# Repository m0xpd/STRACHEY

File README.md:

# STRACHEY

STRACHEY is a new kind of sequencer for electronic music applications. 

STRACHEY's novelty is two-fold: 
* it directly implements my [tuning strategy](https://github.com/m0xpd/TuningStrategyForVoltages) for Klee-type sequencers and
* it introduces a dynamic [Permutation Matrix](https://en.wikipedia.org/wiki/Permutation_matrix) between the gates and the weights, adding a new dimension of variability

I you wish to build one, or if you're just curious, you can read or download [details of the hardware, including PCB and front panel designs](https://github.com/m0xpd/STRACHEY/tree/main/Hardware) and [a listing of the controller code](https://github.com/m0xpd/STRACHEY/tree/main/Controller).

There are some [specifications here](https://github.com/m0xpd/STRACHEY/blob/main/README.md#specifications) and some details of [Calibration and Configuration here](https://github.com/m0xpd/STRACHEY/blob/main/README.md#calibration-and-configuration). 

I have produced an [Introductory video](https://youtu.be/6UQzKo1PWnU), which describes and demonstrates STRACHEY in detail. 

Further description of STRACHEY follows below.

STRACHEY is published under a Creative Commons BY-SA 4.0 [License](https://github.com/m0xpd/STRACHEY/blob/main/LICENSE.txt). 

# Background

The STRACHEY sequencer is named for [Christopher Strachey](https://en.wikipedia.org/wiki/Christopher_Strachey), who (amongst many other accomplishments) was the first person in England to [program a computer to make music](https://link.springer.com/chapter/10.1007/978-3-319-53280-6_8), leading to the world's [first recording of computer-generated music](http://curation.cs.manchester.ac.uk/digital60/www.digital60.org/media/mark_one_digital_music/mark_one_digital_music.mp3).

Christopher Strachey developed [one of the world's first computer games](https://historyofinformation.com/detail.php?entryid=3731), and developed the programming language CPL, a precursor of C (which is used in the code which runs this STRACHEY sequencer).

STRACHEY implements my [Tuning Strategy for Klee-type Sequencers](https://github.com/m0xpd/TuningStrategyForVoltages) and, as such, 
it is directly inspired by Music Thing Modular's [Turing Machine](https://www.musicthing.co.uk/Turing-Machine/) and its [Voltages expander](https://www.musicthing.co.uk/Turing-Volts-Expander/). STRACHEY was built on my own experiences and habits, formed when using the Turing Machine with its Voltages expander; STRACHEY tries to capture and make accessible all which I found *musically useful* within the vast space covered by the Turing Machine. 

STRACHEY contains an implementation of the Turing Machine ('TM'). The control labelled "TURING" at top left of the module (and the associated CV input) is the equivalent of the large, conspicuous knob on the original TM hardware, and operates in exactly the same way. 

STRACHEY offers (almost) all the features of the original hardware, including the ability to interface to expanders, such as [Pulses](https://www.musicthing.co.uk/Turing-Pulse-Expander/), [Volts](https://www.musicthing.co.uk/Turing-Volts-Expander/) and even [Voltages](https://www.musicthing.co.uk/Turing-Volts-Expander/). It even adds several new features to its TM implementation (such as the START output and CV control over both the Length parameter and the Write function).

More importantly, STRACHEY directly implements the fixed tunings presented in my [Tuning Strategy](https://github.com/m0xpd/TuningStrategyForVoltages), without the need to set these up on the sliders of a Voltages expander, which is a laborious and delicate task. This offers opportunity to quickly expand and develop the tunings (e.g. using octave expansions) and - uniquely - to instantly *move between* the tunings, allowing modulations and "chord progressions" to be explored. However, STRACHEY does more...

STRACHEY has three channels of analog output: A, B and Y, all of which derive their timing from a master clock. 

STRACHEY's clock signal can be applied from an external source to the Clock input (as in the TM). In the absence of an external signal, a clock is generated by a simple oscillator integral to STRACHEY. Outputs A and Y both appear on every beat of this clock.

Channel Y is the conventional TM 'OUT' signal, formed of a weighted sum of the TM's gates 1:8  (the weights being an exponential series, proportional to 1, 0.5, 0.25, 0.125, ...). STRACHEY's Y output is scaled to range between 0 and 5V and is provided for use as a general modulation source.

Channel A is the main STRACHEY output. It produces an output (to be interpreted as a 1V/octave pitch CV signal) at the rate of the main signal clock. 
It is set to span six and a half octaves at a resolution of 51 quantisation steps per semitone, meaning there will be less than a 2 cent error in tuning over the system's range, if we can trust the DAC linearity (experience to date has been entirely positive).

# STRACHEY Tunings

The control at top right of the panel, labelled "TUNING", and the associated CV input choose between 24 pre-detemined settings of "weights", equivalent to the slider settings on a Turing Machine 'VOLTAGES' expander, or the knobs on any other sequencer. These weights, together with the gates generated by the Turing Machine, form the channel A (and channel B) outputs.

The weight settings are called 'Tunings' and they are chosen from my [Tuning Strategy](https://github.com/m0xpd/TuningStrategyForVoltages) to be those which give an output which I found to be musically useful. 

The tunings are arranged in three Banks; 
* Bank A are "Basic" Tunings, mainly yielding arpeggiated chords 
* Bank B are mainly MODES
* Bank C are mainly [Symmetric Scales](https://en.wikipedia.org/wiki/Symmetric_scale)

The tunings presently implemented in the code are tabulated below:

| Tuning# | Description | Tuning Strategy # | Bank | Display |
|---|---|---|---|---|
| 0 | Root & Fifth | (3) | A | 10000000 |
| 1 | AEOLIAN (Natural minor) | 14 | A | 01000000 |
| 2 | Minor 7th | 5 | A | 00100000 |
| 3 | Major 7th | 6 | A | 00010000 |
| 4 | Diminished 7th | 8 | A | 00001000 |
| 5 | Augmented | 7 | A | 00000100 |
| 6 | "Sus 7th" Feel | 10 | A | 00000010 |
| 7 | "9th" Feel | 9 | A | 00000001 |
| 8 | Root & Fifth | (3) | A | 10000000 |
| 9 | AEOLIAN | 14 | B | 01000000 |
| 10 | DORIAN | 11 | B | 00100000 |
| 11 | PHRYGIAN | 13 | B | 00010000 |
| 12 | IONIAN | 18 | B | 00001000 |
| 13 | Hexatonic, IONIAN, missing 7th degree | 22 | B | 00000100 |
| 14 | Octatonic, IONIAN, with added flat 5 | 20 | B | 00000010 |
| 15 | Hexatonic, with no third | 23 | B | 00000001 |
| 16 | Root & Octave | (3) | C | 10000000 |
| 17 | Tritone | (15) | C | 01000000 |
| 18 | Augmented | 7 | C | 00100000 |
| 19 | Diminshed | 8 | C | 00010000 |
| 20 | Whole-tone | 16 | C | 00001000 |
| 21 | Chromatic | 17 | C | 00000100 |
| 22 | Major (IONIAN) | 19 | C | 00000010 |
| 23 | Descending Major Scale | N/A | C | 00000001 |

'Bank' (fourth column of the table above) is indicated by the stack of three LEDs in the centre, top of the module. Bank A is indicated by the lowest LED.

'Display' (final column of the table) shows the pattern illuminated on the 'TUNING' LEDs.

A bracket surrounding the Tuning Strategy number in the table above indicates that it is slightly modified relative to the tuning given in the Tuning Strategy document (e.g. by the addition of a second flattened fifth to the tritone, to allow it to sound the octave). Tuning # 23 is unusual and is not derived from the Tuning Strategy. It is included as a test/demonstration case. Tuning # 23  does generate 12TET outputs, but it doesn't produce a particularly pleasant output when used with a gate sequences having more than one active gate. It is intended to be used with a **single active gate**, when it will be heard as a descending major scale.

Some tunings are intentionally repeated in the table above for ease of use - some *appear* repeated, but are different forms (such as the several versions of IONIAN [major scale] tuning which are presented).

STRACHEY goes on to develop outputs using these initial tunings by a series of modifications and manipulations, which are now described.

# Weight Modifications in STRACHEY

Channel B is the secondary STRACHEY output. It operates at the same pitch resolution as channel B but (for reasons which are explained below), the pitch range of channel B is lower than that of channel A. 

The outputs on channel B occur at the onsets of a Euclidean pattern, generated by STRACHEY. This pattern has length determined by the Turing Machine's LENGTH parameter and density determined by STRACHEY's DENSITY controls. LENGTH and DENSITY are both controllable by front panel potentiometers - "DENSITY" is the third of STRACHEY's main potentiometers. Both Length and Density and can further be controlled by CV inputs. 

This makes the onsets of the output from channel B: 

* a subset of the beats of the main system clock,
* a pattern which has rhythmic interest and
* a pattern which can be made to change (by modulating the Density CV input)

The same gate sequence (generated by the Turing Machine) and the same initial weight vector (selected by the TUNING controls) produce the channel A and B outputs, so the *set of allowed pitches* are the same (as described at tedious length in the [Tuning Strategy](https://github.com/m0xpd/TuningStrategyForVoltages)). However, STRACHEY can apply two modifications to the weight vector used in forming the output from channel A. 

Firstly, the initial weight vector can be permuted (i.e. changed in order) before channel A's output is formed, during operation, giving STRACHEY an entirely new dimension of variability relative to other Klee sequencers, including the Turing Machine. STRACHEY performs these permutations using different "Methods", selected by the METHOD control (and associated CV input). These permutations are triggered by "Change" commands, issued either by the CHANGE pushbutton (or the associated CV input). A fuller description appears below. 

Secondly, the initial weight vector can be subject to additions, each of which cause an octave increase in pitch span (under control of the SPAN controls - both potentiometer and CV input). These extend the pitch range of the channel A output, using the same notes as specified in the original tuning, but allowing them to range over a wider span. 

Neither the permutations or the octave extensions of channel A's weight vector are applied to channel B.

So - channel B has a generally reduced pitch span compared to channel A (as there is no octave extension added via SPAN) and there is no variation introduced by permutation. It also has less dense onsets; it '*samples*' notes from the set of pitches within the fundamental range of channel A's pitch distribution on a rhythmic sub-pattern of variable DENSITY. Channel B is particularly useful for forming bass or melody against a fuller, arpeggiated 'continuo' from channel A.

# Permuting the Weights of a Step Sequencer

The idea of introducing permutation between the gates and weights of a Random Looping Sequencer is (as far as I'm aware) novel. 

The practice of stopping and single-stepping a sequencer is, of course, familiar and I have [demonstrated some other effects](https://www.youtube.com/watch?v=kFBzPTS7XLM) obtained with multi-rate or asynchronous scanning of a Klee sequencer. But synchronous permutation of the mapping between gates and weights is less familiar. One notable exception is the idea of reversing the scan direction of a sequencer, (which can be expressed as a simple permutation) and is seen on both 'DIY' sequencers from [MFOS](https://musicfromouterspace.com/analogsynth_new/SEQ16_2006/SEQ16_2006.php) and commercial units from e.g. [Doepfer](https://doepfer.de/a154.htm). 

STRACHEY can - of course - reverse its scan direction, either by flipping the current permutation (Method# 13)  or by resetting to a 'reversed' version of the starting weight vector (Method# 12).

There are other synchronous permutations worth exploring.

Back in 2017 I made a gate sequencer 

which was inspired by patterns used in [Change Ringing](https://en.wikipedia.org/wiki/Change_ringing), a perversely English way of sounding the bells of a Church. These patterns are called "Methods". The key ingredient of Change Ringing is an exploration of the permutations by which a number of bells may be sounded in sequence. In the case of my module, I implemented four of the traditional "Methods"  ([Rounds](https://jaharrison.me.uk/Ringing/Glossary/R.html#rounds), [Plain Hunt](https://en.wikipedia.org/wiki/Plain_hunt), [Grandsire](https://en.wikipedia.org/wiki/Grandsire) and [Plain Bob](https://www.ringing.info/plp/pb8/index.html)) to trigger any number of gates (any "[Stage](https://jaharrison.me.uk/Ringing/Glossary/S.html#stage)") between 4 and 8. Although the sequencer was made as a percussion trigger source rather than in attempt to simulate the sound of church bells, I added - for the purposes of demonstration - two 1V/octave pitch CV outputs, one set to be typical of the diatonic tuning of a ring of bells and one set (for comedic purposes!) to a minor pentatonic scale. 

I was, therefore, entirely familiar with the idea of using permutations in general (and permutations from bell ringing in particular) in a step sequencer. The only further inventive step for me in the development of STRACHEY was the extension of these ideas to a Klee-type sequencer. 

That step involved the introduction of a [permutation matrix](https://en.wikipedia.org/wiki/Permutation_matrix) between the gates and the weights in the scalar product which forms the sequencer output - for both a conventional sequencer and a Klee sequencer. (The actual coding doesn't require matrix methods - it is achieved in [the code](https://github.com/m0xpd/STRACHEY/blob/main/Controller/Code/STRACHEY_Sequencer_1v0.ino) just by indexing within the scalar product. The matrix is just a conceptual and mathematical convenience.)

STRACHEY uses a fixed number of weights ("Stage") to form the pitch output from the gate vector: the eight inherited from the 8 sliders on MTM's Voltages expander. If these 8 weights are seen in analogy with 8 bells (which is the standard stage in a larger bell tower for change ringing), some of STRACHEY's methods for permuting the weights can be related to bell ringing.

STRACHEY currently implements two standard bell ringing methods; "[rounds](https://jaharrison.me.uk/Ringing/Glossary/R.html#rounds)" (which is the bell-ringing term when the permuatation matrix is fixed at the identity matrix)  and "Plain Hunt Major" ('Plain Hunt' is - as we've seen - a [standard algorithm](https://en.wikipedia.org/wiki/Plain_hunt) for changing the permutation matrix and 'Major' is [bell-ringing jargon](https://jaharrison.me.uk/Ringing/Glossary/M.html#major) indicating that the algorithm is applied on a stage of 8 weights) . 

In both cases, STRACHEY will implement [plain courses](https://jaharrison.me.uk/Ringing/Glossary/P.html#plaincourse) of these methods (just as my gate sequencer did back in 2017). However, in STRACHEY there is possibility to introduce variation, described below, similar to a bell-ringing ['single' change](https://jaharrison.me.uk/Ringing/Glossary/S.html#singlechange), by which the hunt may be changed, to extend the sequence to a longer pattern. By this means, STRACHEY can be set in rounds (Method# 0) or plain hunt (Method# 6), using the METHOD controls (potentiometer or CV), and set to run on course, with occasional calls to a random 'single' by changing the METHOD to the random single change call (Method# 5 - all the METHODs are tabulated below).  

STRACHEY can introduce variation by other means.

STRACHEY can *sort* the weights in pitch order, either descending or ascending. It can do this in two ways - either in an immediate sort or as one step of a [bubble sort](https://en.wikipedia.org/wiki/Bubble_sort) (such that a number of successive number of calls to this process are required to achieve the final sort). Each change is made at the start of the cycle (of length determined by the Turing Machine's LENGTH parameter), if requested by an 'Change' input during the previous cycle. 

STRACHEY can also reset the permutation matrix (to the identity matrix - playing 'rounds' in bell-ringing parlance), can fully randomise the permutation matrix or can introduce one random swap in the permutation matrix associated with swapping position of a random weight with one of its neighbours. (This last method is the analogy with the underlying technique in [Call-changing](https://en.wikipedia.org/wiki/Call_changes) - the 'single' described above,  but is - in this case - randomised rather than designed.)

A table of all the (currently implemented) METHODS is presented below, along with the boundaries for the voltages which should be applied at the Method CV input if it is desired to select the METHOD using this means. 

|  Method #   |  Description   |  Vlow   |  Vhigh  |
|------|----|----|----|
|  0  | Reset |  0  |  0.3125  |
|  1  | SortAscending |  0.31  |  0.63  |
|  2  | SortDescending |  0.63  |  0.94 |
|  3  | SingleSortUp |  0.94  |  1.25  |
|  4  | SingleSortDown |  1.25  |  1.56  |
|  5  | RandomSingle |  1.56  |  1.88  |
|  6  | PlainHunt |  1.88  |  2.19  |
|  7  | *Not Implemented*  |  2.19  |  2.5  |
|  8  | RotateR |  2.5  |  2.81  |
|  9  | RotateL |  2.81  |  3.13  |
|  10  | *Not Implemented* |  3.13  |  3.44  |
|  11  | *Not Implemented* |  3.44  |  3.75  |
|  12  | Reverse |  3.75  |  4.06  |
|  13  | Flip |  4.06  |  4.38  |
|  14  | *Not Implemented* |  4.38  |  4.69  |
|  15  | Shuffle |  4.69  |  5  |

Note that the **Method #** is displayed (in binary) on the four red LEDs above the METHOD control. 

The METHOD display will flash after a CHANGE call is made (either by pressing the CHANGE button or pulling down the Change CV input) until the selected subroutine call is completed at the start of the next cycle. For continuous methods such as running Plain Hunt (Method # 6) or continuously flipping the order on successive passes (Method # 13) it is appropriate to keep Change continually asserted (e.g. by tying the Change CV low). The Method LEDs will then flash continually, pausing only on the first beat of each cycle when START=1.      

# Calibration and Configuration

STRACHEY has one aspect requiring **calibration** before it will operate correctly; trimmers TR1 and TR2 must be adjusted to ensure that outputs A and B (respectively) are correctly tuned in V/octave terms. The MC4922 DAC is operated over a 0:5V output range, but the DAC's output is further passed through non-inverting amplifier stages (IC4D for channel A and IC4 C for channel B) with gain of 2. The code expects the full-scale 5V output from the DAC to be broken down into 2^12 steps and uses 51 steps per semitone. 

Accordingly, I have calculated that *in an ideal system* the trimmers should be set to a ratio of 0.669 (i.e. a 1k trimmer should have the lower leg of the potential divider set to 669 Ohms). In reality, where all the components have tolerances and there are some offsets etc., this ratio will not be quite correct - hence the decision to use trimmers rather than fixed resistors. I just measured my own trimmers (which have - so far - been set only 'by ear') and found that TR1 is set at a ratio of 0.696 and TR2 is at a ratio of 0.689. Start off at 0.7 and you'll be close!

There is one feature of STRACHEY that requires **configuration**. There is provided on the main board an Turing Machine expansion port in the standard  Music Thing Modular format. It can be used *either* as a GATES expander (by bridging pins 1 and 2 of JP3, which connects the 'EXP_SEL' (Expander Select) line to 5V) or as a PULSES expander (by bridging pins 2 and 3 of JP3, which connects the 'EXP_SEL' (Expander Select) line to the main clock). The GATES expander port is used with [VOLTS](https://www.musicthing.co.uk/Turing-Volts-Expander/) and [VOLTAGES](https://www.musicthing.co.uk/Turing-Voltages-Expander/) and the PULSES expander port is used with [PULSES](https://www.musicthing.co.uk/Turing-Pulse-Expander/). 

I prefer to use STRACHEY with a [PULSES](https://www.musicthing.co.uk/Turing-Pulse-Expander/) module to expand the time-domain and rhythmic capability of the sequencer; STRACHEY already produces a rich set of analog (pitch) outputs. Accordingly, I set up my expander port as a PULSES expander.

The red stripe on the expander ribbon cable goes towards the bottom edge of STRACHEY's Main board (I forgot to put a marker on the silkscreen). 

# Specifications

**Width:** 

STRACHEY is **18HP wide**.

**Depth:**

STRACHEY extends **43 mm** behind the [front panel](https://github.com/m0xpd/STRACHEY/blob/main/Hardware/Panel/README.md) when a conventional Eurorack power header **with strain relief** is inserted (this is the same depth as the [original Turing Machine](https://www.musicthing.co.uk/Turing-Machine/)).

If your power header doesn't have a strain relief (which is probably more typical, judging by the power cables delivered with commercial modules) the depth is limited by the Arduino's USB receptacle; in this situation STRACHEY extends **42mm** behind the [front panel](https://github.com/m0xpd/STRACHEY/blob/main/Hardware/Panel/README.md).

**Power Consumption:**

| Power Rail | Current |
|---|---|
| +12V | **48mA** |
| -12V | **10mA** |
| 5V | **0** |

(peak currents, measured with nothing connected to STRACHEY's expansion port).

**Miscellaneous:**

All inputs are protected against over/under voltage.

Most of the CV inputs are intended to operate over a 0:5V control range. However, the Density and Method CV inputs are applied to attenuverters; these inputs will respond to signals spanning the entire bipolar Eurorack voltage range (+/- 12V). 

It is my habit to set up my attenuverter controls such that full counterclockwise rotation gives unity gain and full clockwise rotation gives gain of -1. This is **opposite to common practice**.

The external Clock input is triggered by signals exceeding an **(upward) threshold of 1.25V**.

The Change CV input is ACTIVE LOW - it must be pulled low to call one of the CHANGE METHODs and held high to retain the status quo. This input similarly responds to signals exceeding an (upward) threshold of 1.25V but, given the ACTIVE LOW nature of this control, the **downward threshold of 1.05V** is more important.

The Write input is usually held at mid-voltage (2.5V) by an internal resistor network. When an input is applied to the Write CV jack, this 2.5V is disconnected, so any external device should provide a voltage close to 2.5V. Pulling this voltage **below 0.49 V will write a '0'** and **above 4.39 V will write a '1'**.

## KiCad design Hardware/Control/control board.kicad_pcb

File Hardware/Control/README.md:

# Control Board

This folder contains details of STRACHEY's control board, which you see below (component side).

<p width=100%, align="center">

The bottom side of the control board hosts all the jacks, pots, tactile switches, and 24 LEDs, which mate with the Front Panel and form the user interface.

You can download the main board's schematic as a [.sch file](https://github.com/m0xpd/STRACHEY/blob/main/Hardware/Control/control%20board.kicad_sch) into your PCB program (KiCad etc) or download a [PDF version](https://github.com/m0xpd/STRACHEY/blob/main/Hardware/Control/control%20board%20schematic.pdf).

In addition to the front panel / UI components mentioned above, the control board hosts three 74HC595 serial in, parallel out shift registers. One of these communicates gate signals from inside the Aruino to the physical world - for display on the LEDs, for application to the DAC which drives the channel Y output, and for gate 1 output. The other 2 shift registers service all the other status indication lights. 

The control board also hosts a single quad op-amp, which implements the attenuverter and mixer stages that form the TUNE and DENSITY controls.

STRACHEY is my first electronic project in KiCad and I am new to the BoM generator's .csv output format. I have decided to save this information [as an Excel file](https://github.com/m0xpd/STRACHEY/blob/main/Hardware/Control/Strachey%20Control%20Board%20BoM.xlsx) to retain some edits I made. 

There are a few points in the BoM which should be emphasised, as the information is not made explicit in the schematic.

Firstly, whilst all potentiometers use the 9mm snap-in vertical footprint, only three are the usual 'Alpha' pots. These are VR2 (The TUNING Control), VR5 (The DENSITY control) & VR8 (The TURING Control). The remaining potentiometers are Song Huei 9mm Trimmers

Secondly, the momentary action 6mm 'tactile' switches, SW1:SW3 should be of 13mm size (or taller). The tip of the shaft of a 13mm switch protrudes through the front panel by a little over 1.5mm, which looks and feels right. If you want more, fit a 14mm or 15mm switch.

Finally, although the PCB shows a 3mm LED footprint, the front panel is drilled to accept 2mm "Lighthouse-type" LEDs. I have chosen to use green LEDs for the TUNING indication (LEDs 13:17, 19, 21 & 23) whilst the rest are red. Series resistors of 1K for the green and 10k for the red work well with the particular LEDs I'm using - hence the component values for the resistor networks RN1 & 2 etc.. However, you should check **YOUR** LEDs for appropriate brightness before fitting the resistors. 

The [.pcb file](https://github.com/m0xpd/STRACHEY/blob/main/Hardware/Control/control%20board.kicad_pcb) and [.pro file](https://github.com/m0xpd/STRACHEY/blob/main/Hardware/Control/control%20board.kicad_pro) (togther with the [.sch file](https://github.com/m0xpd/STRACHEY/blob/main/Hardware/Control/control%20board.kicad_sch) ) constitute a KiCad project, which define the Main board. 

[JLCPCB](https://jlcpcb.com) made the boards for my prototype and did their usual excellent job (usual disclaimer) - you can see the top and bottom sides of the Control Board below:

<p width=100%, align="center">

# Assembly

As with all such 'control boards' which mate with an accurately prepared [front panel](https://github.com/m0xpd/STRACHEY/blob/main/Hardware/Panel/README.md), it is advisable to fit the panel-mounting components into BOTH the PCB and panel *DURING soldering*, to ensure correct alignment. 

This is **particularly important** with all the tiny LEDs in STRACHEY, as alignment is critical!

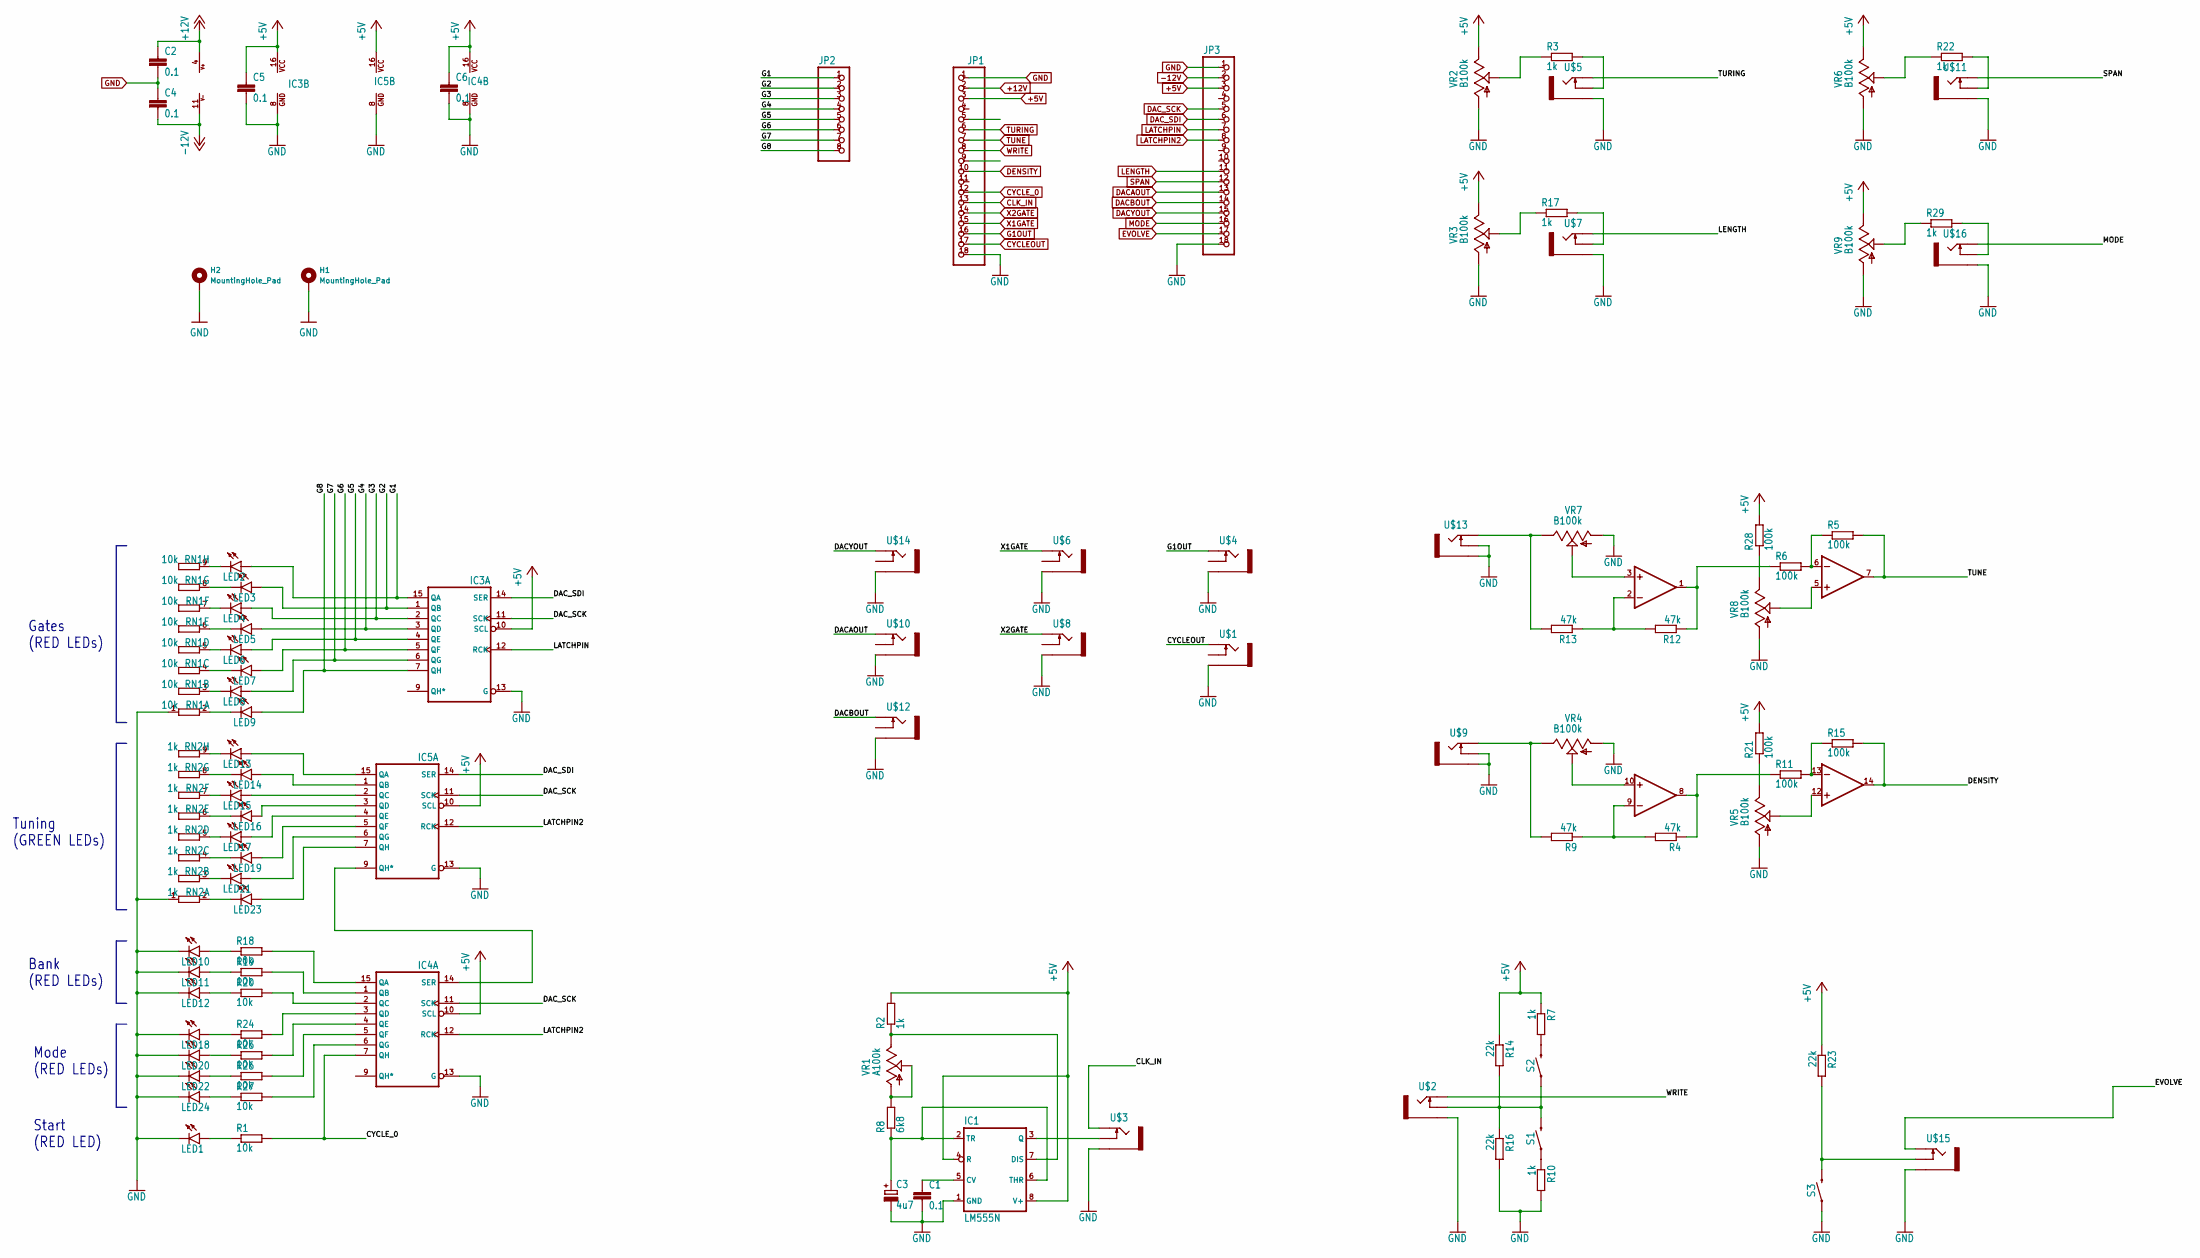
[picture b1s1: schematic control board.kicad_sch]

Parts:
C1, C2, C4, C5, C6: 0.1; C050-025X075
C3: 4u7; E2,5-5
H1, H2: MountingHole_Pad; MountingHole_3.2mm_M3_DIN965_Pad_TopBottom
IC1: LM555N; DIL08
IC2: TL084P; DIL14
IC3, IC4, IC5: 74HC595N; DIL16
JP1, JP3: 1X18
JP2: 1X08
LED1, LED2, LED3, LED4, LED5, LED6, LED7, LED8, LED9, LED10, LED11, LED12, LED13, LED14, LED15, LED16, LED17, LED18, LED19, LED20, LED21, LED22, LED23, LED24: LED3MM
R1, R18, R19, R20, R24, R25, R26, R27: 10k; 0204_7
R2, R3, R7, R10, R17, R22, R29: 1k; 0204_7
R4, R9, R12, R13: 47k; 0204_7
R5, R6, R11, R15, R21, R28: 100k; 0204_7
R8: 6k8; 0204_7
R14, R16, R23: 22k; 0204_7
RN1: 10k; SIL9
RN2: 1k; SIL9
S1, S2, S3: MOMENTARY-SWITCH-SPST-PTH-6.0MM; TACTILE_SWITCH_PTH_6.0MM
U$1, U$2, U$3, U$4, U$5, U$6, U$7, U$8, U$9, U$10, U$11, U$12, U$13, U$14, U$15, U$16: THONKICONN_JACK; WQP-PJ301M-12_JACK
VR1: A100k; 9MM_SNAP-IN_POT
VR2, VR3, VR4, VR5, VR6, VR7, VR8, VR9: B100k; 9MM_SNAP-IN_POT

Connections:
+5V: C5.1, C6.1, IC1.4 (R), IC1.8 (V+), IC3.10 (SCL), IC3.16 (VCC), IC4.10 (SCL), IC4.16 (VCC), IC5.10 (SCL), IC5.16 (VCC), JP1.3, JP3.3, R2.2, R7.1, R14.1, R21.2, R23.1, R28.2, VR2.3 (E), VR3.3 (E), VR6.3 (E), VR9.3 (E)
+12V: C2.1, IC2.4 (V+), JP1.2
-12V: C4.2, IC2.11 (V-), JP3.2
/G1: IC3.15 (QA), JP2.1, LED2.A
/G2: IC3.1 (QB), JP2.2, LED3.A
/G3: IC3.2 (QC), JP2.3, LED4.A
/G4: IC3.3 (QD), JP2.4, LED5.A
/G5: IC3.4 (QE), JP2.5, LED6.A
/G6: IC3.5 (QF), JP2.6, LED7.A
/G7: IC3.6 (QG), JP2.7, LED8.A
/G8: IC3.7 (QH), JP2.8, LED9.A
CLK_IN: JP1.13, U$3.P$1_TIP (TIP)
CYCLEOUT: JP1.17, U$1.P$1_TIP (TIP)
CYCLE_0: IC4.7 (QH), JP1.12, R1.2
DACAOUT: JP3.13, U$10.P$1_TIP (TIP)
DACBOUT: JP3.14, U$12.P$1_TIP (TIP)
DACYOUT: JP3.15, U$14.P$1_TIP (TIP)
DAC_SCK: IC3.11 (SCK), IC4.11 (SCK), IC5.11 (SCK), JP3.5
DAC_SDI: IC3.14 (SER), IC5.14 (SER), JP3.6
DENSITY: IC2.14 (OUT), JP1.10, R15.2
EVOLVE: JP3.17, U$15.P$1_TIP (TIP)
G1OUT: JP1.16, U$4.P$1_TIP (TIP)
GND: C1.2, C2.2, C3.-, C4.1, C5.2, C6.2, H1.1, H2.1, IC1.1 (GND), IC3.8 (GND), IC3.13 (G), IC4.8 (GND), IC4.13 (G), IC5.8 (GND), IC5.13 (G), JP1.1, JP1.18, JP3.1, JP3.18, LED1.K (C), LED10.K (C), LED11.K (C), LED12.K (C), LED18.K (C), LED20.K (C), LED22.K (C), LED24.K (C), R10.2, R16.2, RN1.1, RN2.1, S3.1, U$1.P$3_SLEEVE (SLEEVE), U$2.P$3_SLEEVE (SLEEVE), U$3.P$3_SLEEVE (SLEEVE), U$4.P$3_SLEEVE (SLEEVE), U$5.P$3_SLEEVE (SLEEVE), U$6.P$3_SLEEVE (SLEEVE), U$7.P$3_SLEEVE (SLEEVE), U$8.P$3_SLEEVE (SLEEVE), U$9.P$2_SWITCH (SWITCH), U$9.P$3_SLEEVE (SLEEVE), U$10.P$3_SLEEVE (SLEEVE), U$11.P$3_SLEEVE (SLEEVE), U$12.P$3_SLEEVE (SLEEVE), U$13.P$2_SWITCH (SWITCH), U$13.P$3_SLEEVE (SLEEVE), U$14.P$3_SLEEVE (SLEEVE), U$15.P$3_SLEEVE (SLEEVE), U$16.P$3_SLEEVE (SLEEVE), VR2.1 (A), VR3.1 (A), VR4.1 (A), VR5.1 (A), VR6.1 (A), VR7.1 (A), VR8.1 (A), VR9.1 (A)
LATCHPIN: IC3.12 (RCK), JP3.7
LATCHPIN2: IC4.12 (RCK), IC5.12 (RCK), JP3.8
LENGTH: JP3.11, U$7.P$1_TIP (TIP)
MODE: JP3.16, U$16.P$1_TIP (TIP)
unnamed: IC5.15 (QA), LED13.A
unnamed: IC5.1 (QB), LED14.A
unnamed: IC5.2 (QC), LED15.A
unnamed: IC5.3 (QD), LED16.A
unnamed: IC5.4 (QE), LED17.A
unnamed: IC5.5 (QF), LED19.A
unnamed: IC5.6 (QG), LED21.A
unnamed: IC5.7 (QH), LED23.A
unnamed: IC4.14 (SER), IC5.9 (QH*)
unnamed: IC4.15 (QA), R18.2
unnamed: IC4.1 (QB), R19.2
unnamed: IC4.2 (QC), R20.2
unnamed: IC4.3 (QD), R24.2
unnamed: IC4.4 (QE), R25.2
unnamed: IC4.5 (QF), R26.2
unnamed: IC4.6 (QG), R27.2
unnamed: C1.1, IC1.5 (CV)
unnamed: IC1.7 (DIS), R2.1, VR1.3 (E)
unnamed: IC1.3 (Q), U$3.P$2_SWITCH (SWITCH)
unnamed: C3.+, IC1.2 (TR), IC1.6 (THR), R8.1
unnamed: IC2.3 (+IN), VR7.2 (S)
unnamed: IC2.2 (-IN), R12.2, R13.1
unnamed: IC2.1 (OUT), R6.1, R12.1
unnamed: IC2.5 (+IN), VR8.2 (S)
unnamed: IC2.6 (-IN), R5.1, R6.2
unnamed: IC2.10 (+IN), VR4.2 (S)
unnamed: IC2.9 (-IN), R4.2, R9.1
unnamed: IC2.8 (OUT), R4.1, R11.1
unnamed: IC2.12 (+IN), VR5.2 (S)
unnamed: IC2.13 (-IN), R11.2, R15.1
unnamed: LED2.K (C), RN1.9 (2)
unnamed: LED3.K (C), RN1.8 (2)
unnamed: LED4.K (C), RN1.7 (2)
unnamed: LED5.K (C), RN1.6 (2)
unnamed: LED6.K (C), RN1.5 (2)
unnamed: LED7.K (C), RN1.4 (2)
unnamed: LED8.K (C), RN1.3 (2)
unnamed: LED9.K (C), RN1.2
unnamed: LED13.K (C), RN2.9 (2)
unnamed: LED14.K (C), RN2.8 (2)
unnamed: LED15.K (C), RN2.7 (2)
unnamed: LED16.K (C), RN2.6 (2)
unnamed: LED17.K (C), RN2.5 (2)
unnamed: LED19.K (C), RN2.4 (2)
unnamed: LED21.K (C), RN2.3 (2)
unnamed: LED23.K (C), RN2.2
unnamed: LED10.A, R18.1
unnamed: LED11.A, R19.1
unnamed: LED12.A, R20.1
unnamed: LED18.A, R24.1
unnamed: LED20.A, R25.1
unnamed: LED22.A, R26.1
unnamed: LED24.A, R27.1
unnamed: LED1.A, R1.1
unnamed: R10.1, S1.1
unnamed: R7.2, S2.3 (2)
unnamed: R14.2, R16.1, S1.3 (2), S2.1, U$2.P$2_SWITCH (SWITCH)
unnamed: R23.2, S3.3 (2), U$15.P$2_SWITCH (SWITCH)
unnamed: R3.2, U$5.P$2_SWITCH (SWITCH)
unnamed: R17.2, U$7.P$2_SWITCH (SWITCH)
unnamed: R22.2, U$11.P$2_SWITCH (SWITCH)
unnamed: R13.2, U$13.P$1_TIP (TIP), VR7.3 (E)
unnamed: R9.2, U$9.P$1_TIP (TIP), VR4.3 (E)
unnamed: R29.2, U$16.P$2_SWITCH (SWITCH)
unnamed: R8.2, VR1.1 (A), VR1.2 (S)
unnamed: R3.1, VR2.2 (S)
unnamed: R17.1, VR3.2 (S)
unnamed: R22.1, VR6.2 (S)
unnamed: R28.1, VR8.3 (E)
unnamed: R21.1, VR5.3 (E)
unnamed: R29.1, VR9.2 (S)
SPAN: JP3.12, U$11.P$1_TIP (TIP)
TUNE: IC2.7 (OUT), JP1.7, R5.2
TURING: JP1.6, U$5.P$1_TIP (TIP)
WRITE: JP1.8, U$2.P$1_TIP (TIP)
X1GATE: JP1.15, U$6.P$1_TIP (TIP)
X2GATE: JP1.14, U$8.P$1_TIP (TIP)

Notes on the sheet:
Tuning (GREEN LEDs)
Bank (RED LEDs)
Start (RED LED)
Mode (RED LEDs)
Gates (RED LEDs)

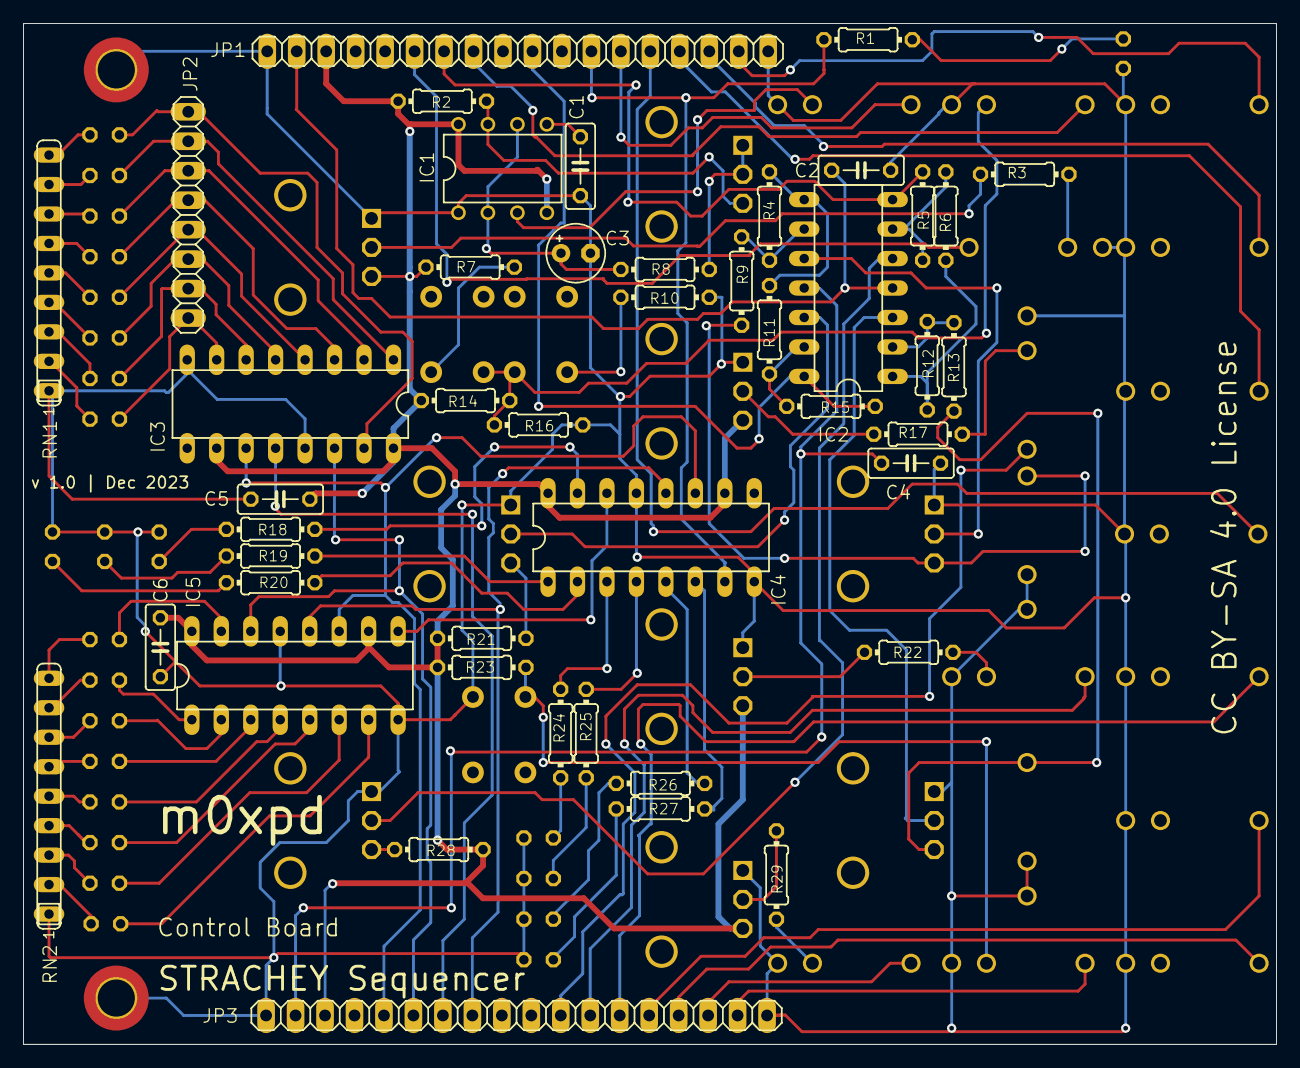
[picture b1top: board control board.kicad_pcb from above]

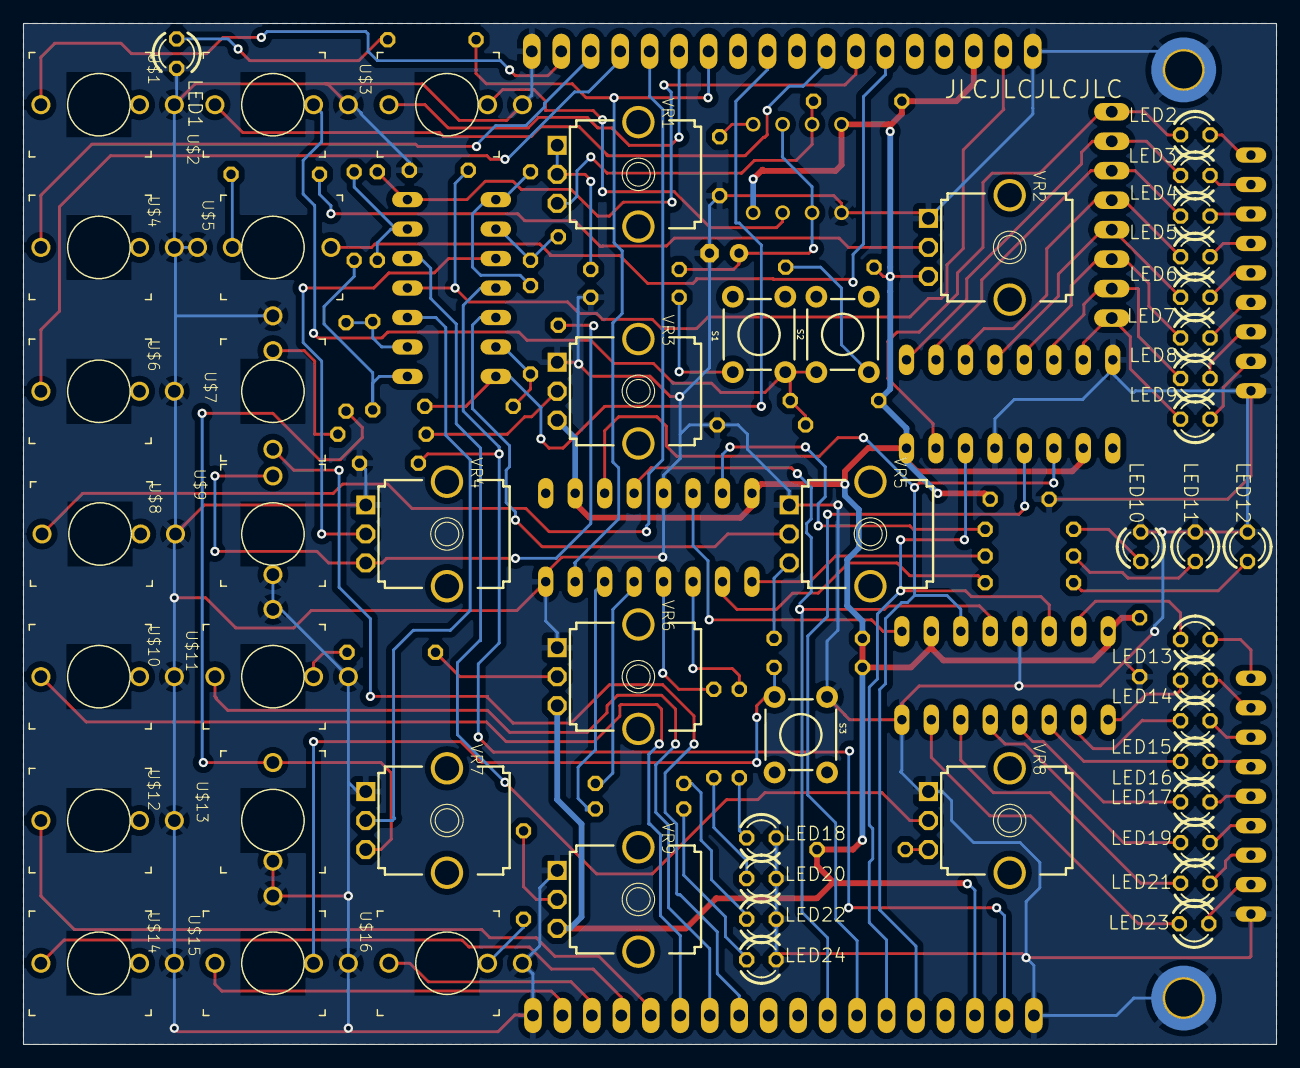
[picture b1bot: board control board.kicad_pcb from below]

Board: 2 copper layers, 108.0 x 88.0 mm, 99 parts (52 on the bottom side), 104 nets.

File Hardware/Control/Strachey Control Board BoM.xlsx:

Source: | xxx
Date: | xxx
Tool: | Eeschema 7.0.9
Generator: | /Applications/KiCad/KiCad.app/Contents/SharedSupport/plugins/bom_csv_grouped_by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
Component Count: | 99
Collated Components:
Item | Qty | Reference(s) | Value | Comments | LibPart | Footprint | Datasheet | DNP
1 | 5 | C1, C2, C4, C5, C6 | 0.1u |  | control board-eagle-import:C-EU050-025X075 | control board:C050-025X075
2 | 1 | C3 | 4u7 |  | control board-eagle-import:CPOL-EUE2.5-5 | control board:E2,5-5
3 | 2 | H1, H2 | MountingHole_Pad |  | Mechanical:MountingHole_Pad | MountingHole:MountingHole_3.2mm_M3_DIN965_Pad_TopBottom | ~
4 | 1 | IC1 | LM555N |  | control board-eagle-import:555N | control board:DIL08
5 | 1 | IC2 | TL084P |  | control board-eagle-import:TL084P | control board:DIL14
6 | 3 | IC3, IC4, IC5 | 74HC595N |  | control board-eagle-import:74595N | control board:DIL16
7 | 2 | JP1, JP3 |  | 1*18 0.1 inch FEMALE Header | control board-eagle-import:PINHD-1X18 | control board:1X18
8 | 1 | JP2 |  | 1*8 0.1 inch FEMALE Header | control board-eagle-import:PINHD-1X8 | control board:1X08
9 | 24 | LED1, LED2, LED3, LED4, LED5, LED6, LED7, LED8, LED9, LED10, LED11, LED12, LED1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 |  | 2mm 'Lighthouse' LED LEDs13:17, 19, 21 & 23 GREEN, remainder RED | control board-eagle-import:LED3MM | control board:LED3MM
10 | 8 | R1, R18, R19, R20, R24, R25, R26, R27 | 10k |  | control board-eagle-import:R-EU_0204/7 | control board:0204_7
11 | 7 | R2, R3, R7, R10, R17, R22, R29 | 1k |  | control board-eagle-import:R-EU_0204/7 | control board:0204_7
12 | 4 | R4, R9, R12, R13 | 47k |  | control board-eagle-import:R-EU_0204/7 | control board:0204_7
13 | 6 | R5, R6, R11, R15, R21, R28 | 100k |  | control board-eagle-import:R-EU_0204/7 | control board:0204_7
14 | 1 | R8 | 6k8 |  | control board-eagle-import:R-EU_0204/7 | control board:0204_7
15 | 3 | R14, R16, R23 | 22k |  | control board-eagle-import:R-EU_0204/7 | control board:0204_7
16 | 1 | RN1 | 10k |  | control board-eagle-import:GE08R | control board:SIL9
17 | 1 | RN2 | 1k |  | control board-eagle-import:GE08R | control board:SIL9
18 | 3 | S1, S2, S3 | MOMENTARY-SWITCH-SPST-PTH-6.0MM | 6*6*13 mm momentary action tactile switches | control board-eagle-import:MOMENTARY-SWITCH-SPST-PTH-6.0MM | control board:TACTILE_SWITCH_PTH_6.0MM
19 | 16 | U$1, U$2, U$3, U$4, U$5, U$6, U$7, U$8, U$9, U$10, U$11, U$12, U$13, U$14, U$15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 | THONKICONN_JACK | https://www.thonk.co.uk/shop/thonkiconn/ | control board-eagle-import:THONKICONN_JACK | control board:WQP-PJ301M-12_JACK
20 | 1 | VR1 | A100k | Song Huei Trimmer Pots, eg: https://www.thonk.co.uk/shop/ttpots/ | control board-eagle-import:9MM_SNAP-IN_POT_ | control board:9MM_SNAP-IN_POT
21 | 3 | VR2, VR5, VR8 | B100k | Alpha 9mm pots, eg: https://www.thonk.co.uk/shop/alpha-9mm-pots-vertical-t18/ | control board-eagle-import:9MM_SNAP-IN_POT_ | control board:9MM_SNAP-IN_POT
22 | 5 | VR3, VR4, VR6, VR7, VR9 | B100k | Song Huei Trimmer Pots, eg: https://www.thonk.co.uk/shop/ttpots/

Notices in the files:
Controller/STRACHEY_Sequencer_1v0.ino:
and includes a new software implementation of the Turing Machine, an
open-source (CC BY-SA) design from Music Thing Modular.
This code published under Creative Commons CC BY-SA 4.0 License
